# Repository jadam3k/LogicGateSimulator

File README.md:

# LogicGateSimulator
Simple Logic Gate Simulator using arduino Nano
I'm studying industrial automation, so I figured something like this would be useful, especially since Boolean algebra is important in automation. The project didn't take long and is interesting.

### Schema

### PCB

### 3D PCB

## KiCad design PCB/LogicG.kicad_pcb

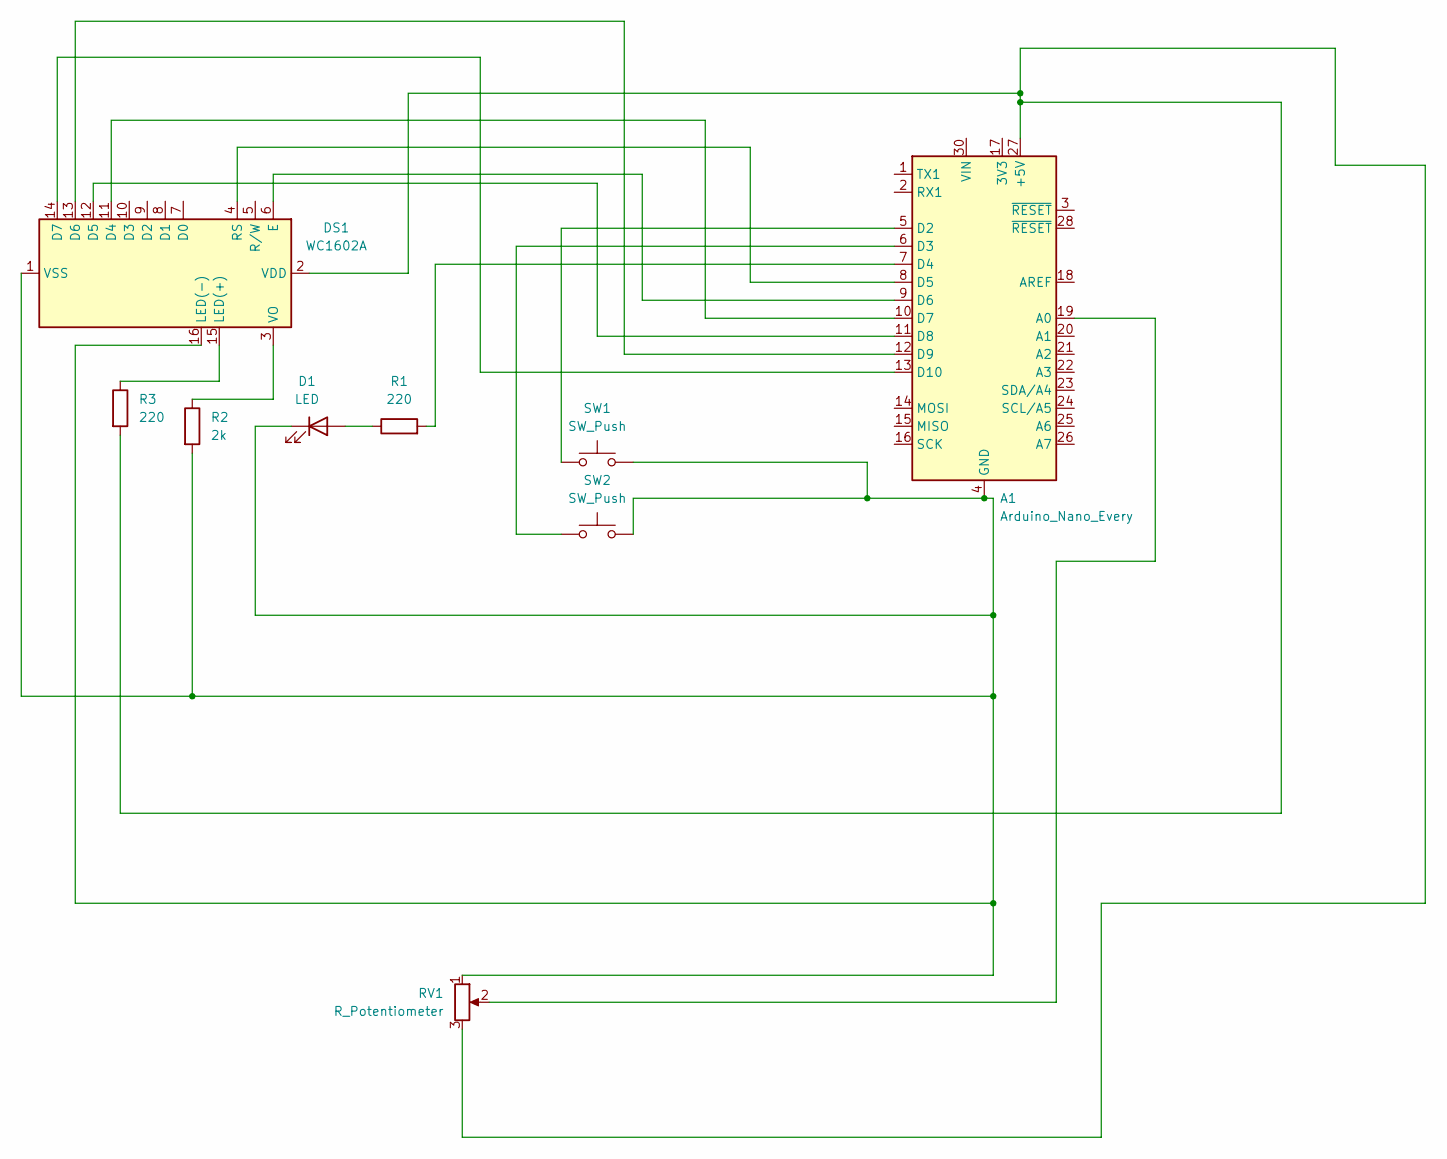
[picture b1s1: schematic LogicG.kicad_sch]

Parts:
A1: Arduino_Nano_Every; Arduino_Nano
D1: LED; LED_D8.0mm
DS1: WC1602A
R1, R3: 220; R_Axial_DIN0207_L6.3mm_D2.5mm_P15.24mm_Horizontal
R2: 2k; R_Axial_DIN0207_L6.3mm_D2.5mm_P15.24mm_Horizontal
RV1: R_Potentiometer; Potentiometer_Bourns_3296P_Horizontal
SW1, SW2: SW_Push; SW_PUSH-12mm

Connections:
unnamed: A1.27 (+5V), DS1.2 (VDD), R3.2, RV1.3
unnamed: A1.19 (A0), RV1.2
unnamed: A1.5 (D2), SW1.1
unnamed: A1.6 (D3), SW2.1
unnamed: A1.7 (D4), R1.2
unnamed: A1.8 (D5), DS1.4 (RS)
unnamed: A1.9 (D6), DS1.6 (E)
unnamed: A1.10 (D7), DS1.11 (D4)
unnamed: A1.11 (D8), DS1.12 (D5)
unnamed: A1.12 (D9), DS1.13 (D6)
unnamed: A1.13 (D10), DS1.14 (D7)
unnamed: D1.2 (A), R1.1
unnamed: A1.4 (GND), A1.29 (GND), D1.1 (K), DS1.1 (VSS), DS1.16 (LED(-)), R2.2, RV1.1, SW1.2, SW2.2
unnamed: DS1.15 (LED(+)), R3.1
unnamed: DS1.3 (VO), R2.1

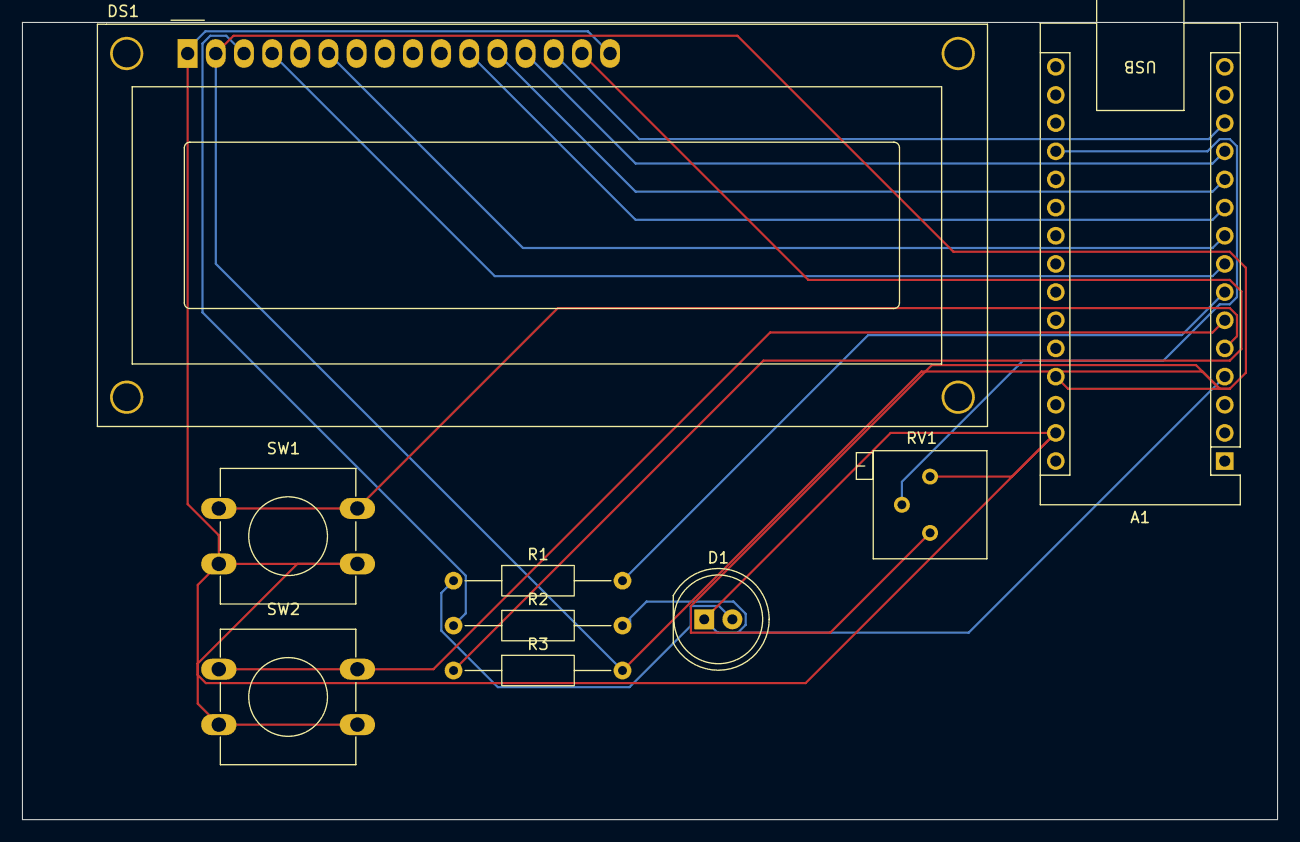
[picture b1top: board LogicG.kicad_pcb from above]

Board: 2 copper layers, 113.2 x 71.9 mm, 9 parts (0 on the bottom side), 15 nets.

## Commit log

2025-10-29 siema
2025-10-29 Rename Main.py to Main.cpp
